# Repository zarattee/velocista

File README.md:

# velocista
 robot seguidor de linea

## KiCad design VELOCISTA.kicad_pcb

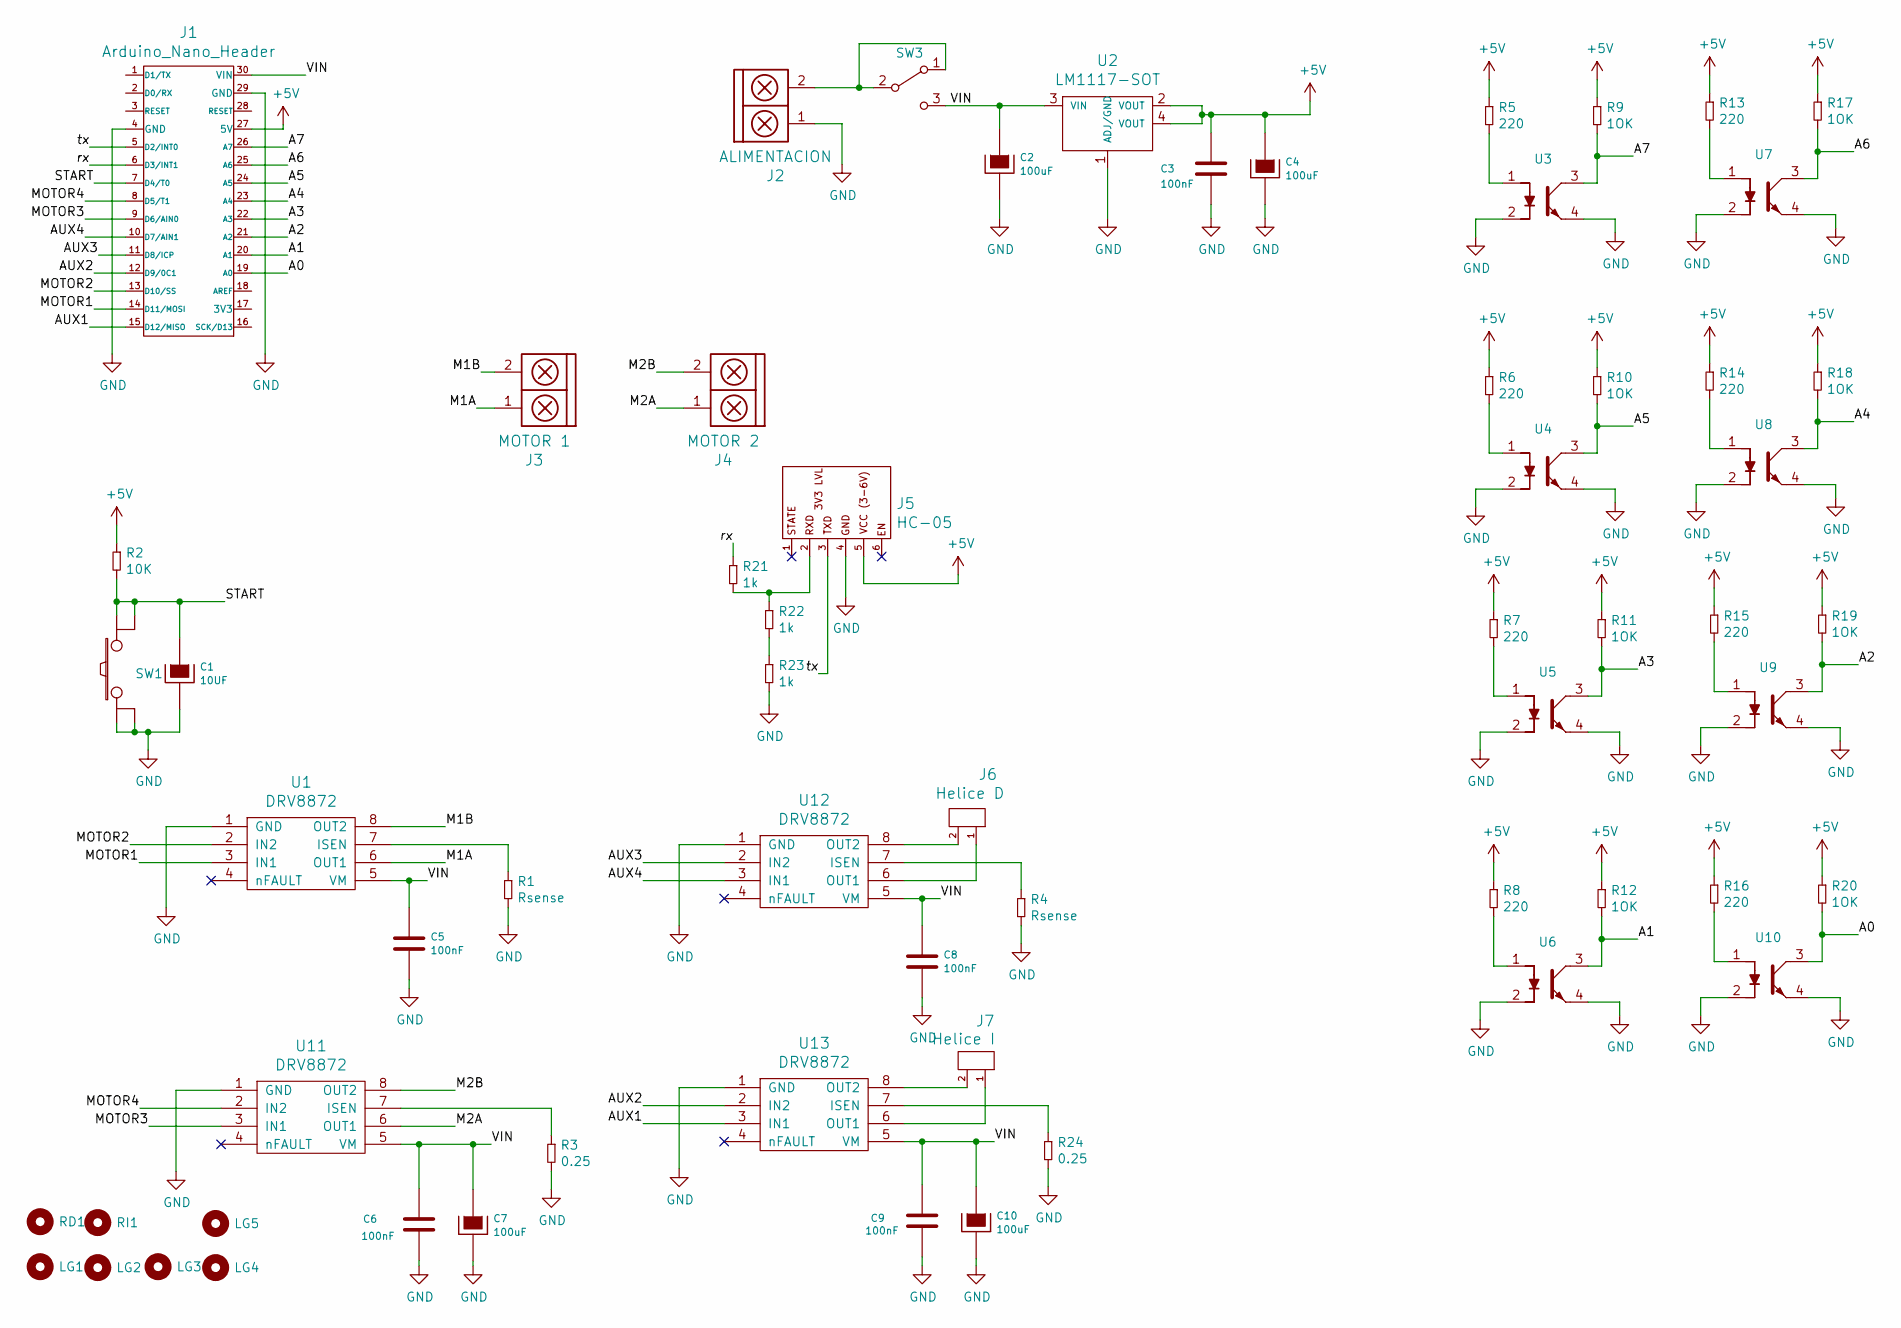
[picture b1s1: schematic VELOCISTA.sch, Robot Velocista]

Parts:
C1: 10UF; CAP_TAN_A
C2: 100uF; CAP_TAN_A
C3: 100nF; C_1206
C4: 100uF; CAP_ELEC_5x11mm
C5, C6, C8, C9: 100nF; CAP_0.1
C7, C10: 100uF; CAP_ELEC_8x11.5mm
J1: Arduino_Nano_Header; arduino_nano_header
J2: ALIMENTACION; BORNERA2_DUO
J3: MOTOR 1; BORNERA2_AZUL
J4: MOTOR 2; BORNERA2_AZUL
J5: HC-05
J6: Helice D; BORNERA2_DUO
J7: Helice I; BORNERA2_DUO
LG1: Mounting_Hole; LOGO_EESTN5
LG2: Mounting_Hole; Logo_Zarate
LG3: Mounting_Hole; Logo_Zarate_Nombre
LG4, LG5: Mounting_Hole; Logo_Rayo
R1, R4: Rsense; R_1206
R2: 10K; R_1206
R3, R24: 0.25; R_1206
R5, R6, R7, R8, R13, R14, R15, R16: 220; R_1206
R9, R10, R11, R12, R17, R18, R19, R20: 1OK; R_1206
R21, R22, R23: 1k; R_1206
RD1: Mounting_Hole; Pololu_Micro_Con_Soporte_Simple
RI1: Mounting_Hole; Pololu_Micro_Con_Soporte_Simple
SW1: SW_PUSH; Pulsador_4_SMD
SW3: SW_SPDT; SW_SPDT_TH_Vertical
U1, U11, U12, U13: DRV8872; SSOP-8
U2: LM1117-SOT; SOT223
U3, U4, U5, U6, U7, U8, U9, U10: QRE1113; QRE1113GR

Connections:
+5V: C3.1, C4.1, J1.27 (5V), J5.5, R2.1, R5.1, R6.1, R7.1, R8.1, R9.1, R10.1, R11.1, R12.1, R13.1, R14.1, R15.1, R16.1, R17.1, R18.1, R19.1, R20.1, U2.2 (VOUT), U2.4 (VOUT)
/A0: J1.19 (A0), R20.2, U10.3
/A1: J1.20 (A1), R12.2, U6.3
/A2: J1.21 (A2), R19.2, U9.3
/A3: J1.22 (A3), R11.2, U5.3
/A4: J1.23 (A4), R18.2, U8.3
/A5: J1.24 (A5), R10.2, U4.3
/A6: J1.25 (A6), R17.2, U7.3
/A7: J1.26 (A7), R9.2, U3.3
/AUX1: J1.15 (D12/MISO), U13.3 (IN1)
/AUX2: J1.12 (D9/0C1), U13.2 (IN2)
/AUX3: J1.11 (D8/ICP), U12.2 (IN2)
/AUX4: J1.10 (D7/AIN1), U12.3 (IN1)
/M1A: J3.1, U1.6 (OUT1)
/M1B: J3.2, U1.8 (OUT2)
/M2A: J4.1, U11.6 (OUT1)
/M2B: J4.2, U11.8 (OUT2)
/MOTOR1: J1.14 (D11/MOSI), U1.3 (IN1)
/MOTOR2: J1.13 (D10/SS), U1.2 (IN2)
/MOTOR3: J1.9 (D6/AIN0), U11.3 (IN1)
/MOTOR4: J1.8 (D5/T1), U11.2 (IN2)
/START: C1.1, J1.7 (D4/T0), R2.2, SW1.3, SW1.4
/VIN: C2.1, C5.1, C6.1, C7.1, C8.1, C9.1, C10.1, J1.30 (VIN), SW3.3 (C), U1.5 (VM), U2.3 (VIN), U11.5 (VM), U12.5 (VM), U13.5 (VM)
/rx: J1.6 (D3/INT1), R21.1
/tx: J1.5 (D2/INT0), J5.3
GND: C1.2, C2.2, C3.2, C4.2, C5.2, C6.2, C7.2, C8.2, C9.2, C10.2, J1.4 (GND), J1.29 (GND), J2.1, J5.4, R1.2, R3.2, R4.2, R23.2, R24.2, SW1.1, SW1.2, U1.1 (GND), U2.1 (ADJ/GND), U3.2, U3.4, U4.2, U4.4, U5.2, U5.4, U6.2, U6.4, U7.2, U7.4, U8.2, U8.4, U9.2, U9.4, U10.2, U10.4, U11.1 (GND), U12.1 (GND), U13.1 (GND)
unnamed: J2.2, SW3.1 (A), SW3.2 (B)
unnamed: J5.2, R21.2, R22.1
unnamed: J6.1, U12.6 (OUT1)
unnamed: J6.2, U12.8 (OUT2)
unnamed: J7.1, U13.6 (OUT1)
unnamed: J7.2, U13.8 (OUT2)
unnamed: R1.1, U1.7 (ISEN)
unnamed: R3.1, U11.7 (ISEN)
unnamed: R4.1, U12.7 (ISEN)
unnamed: R5.2, U3.1
unnamed: R6.2, U4.1
unnamed: R7.2, U5.1
unnamed: R8.2, U6.1
unnamed: R13.2, U7.1
unnamed: R14.2, U8.1
unnamed: R15.2, U9.1
unnamed: R16.2, U10.1
unnamed: R22.2, R23.1
unnamed: R24.1, U13.7 (ISEN)

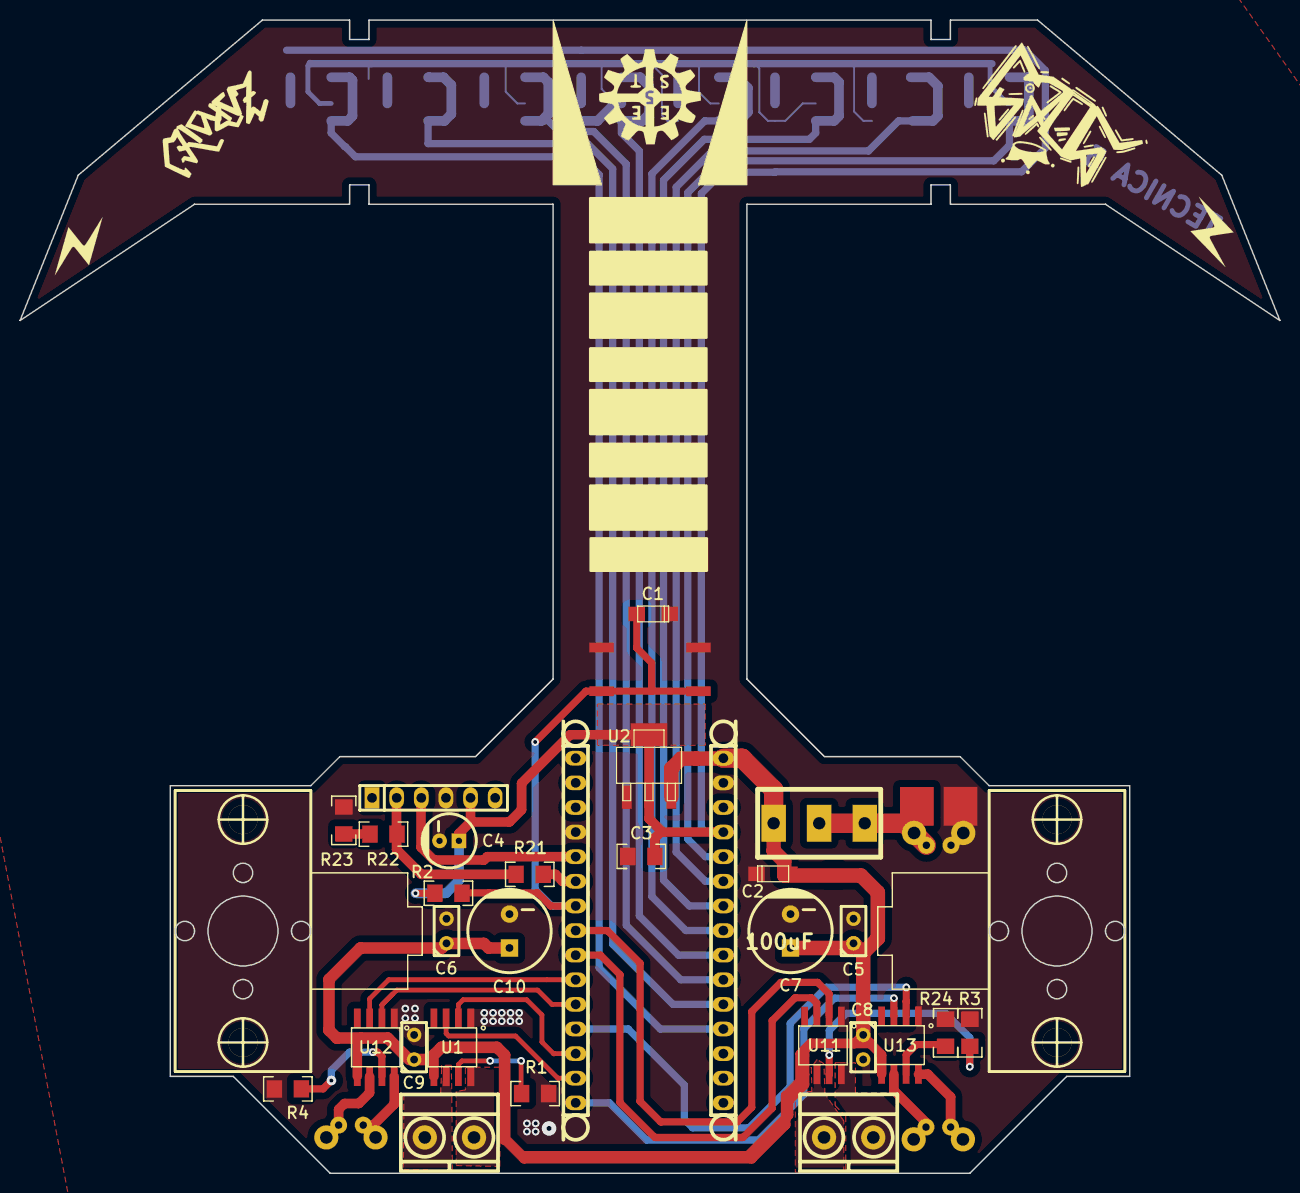
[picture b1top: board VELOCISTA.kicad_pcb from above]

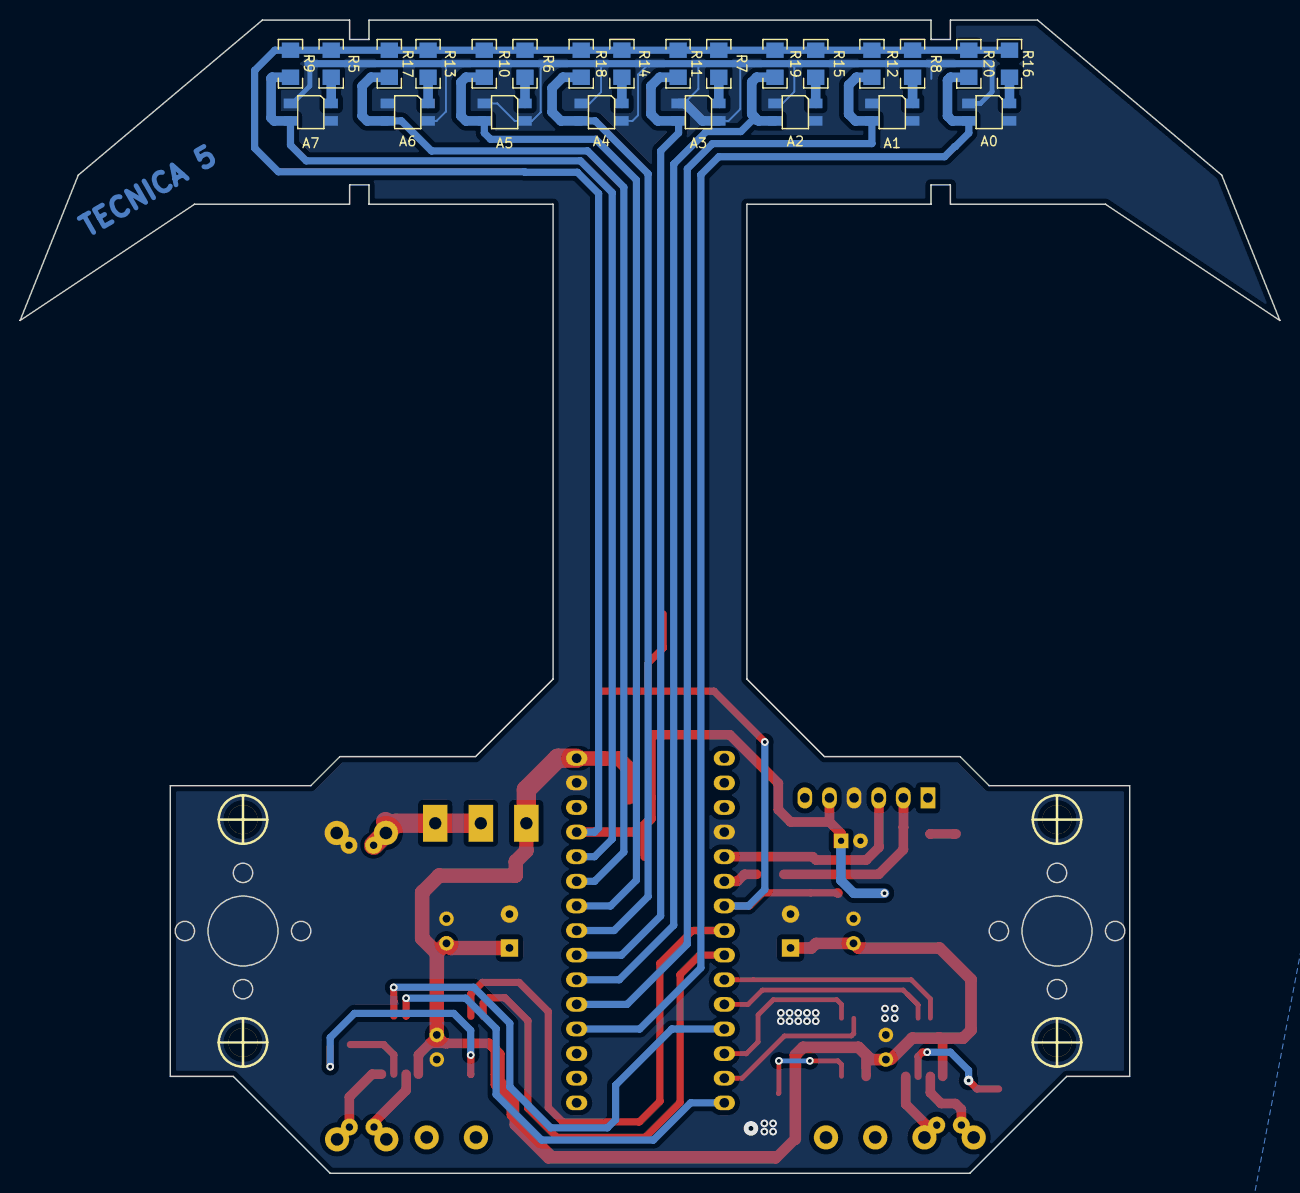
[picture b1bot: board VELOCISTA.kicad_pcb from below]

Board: 2 copper layers, 130.0 x 119.0 mm, 63 parts (24 on the bottom side), 45 nets.

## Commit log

2020-10-19 actualizacion inicial
2020-10-19 Pinout Atmega328p
    Grafica con descripcion de los pines del uC utilizado
2020-10-19 How to gerbers
    Guía para la generación de archivos de fabricación
2020-10-19 Ejemplo de modificación cruzada
    Recomendación para Elias
2020-10-20 se ignora variable de entorno
    se agrego un archivo no aceptable
2020-10-20 Render & BOM
    Generación de las imagenes del modelo 3D del proyecto desde diferentes vistas/configuraciones.
    Incorporación de la lista de materiales interactiva.
2020-10-20 eliminacion de archivos innecesarios
    eleminacion de archivos en conflicot con los archivo originales
2020-10-30 Actualizacion del archivo de taladros
    Se actualizo el archivo de taladros verificando el formato requerido por el fabricante.
    Se agrego la captura de pantalla de la configuracion utilizada para futura referencia.
    Se agrego el archivo comprimido con los gerbers enviados al fabricante.
2020-11-06 lista de componentes
    se agrego lista de componentees de la placa
2020-11-27 se agrega lista de componentes
    se agrega lista de componentes y
    como proveedor https://www.digikey.com
2021-01-08 Actualización BOM
    Se cambió el formato de la lista de materiales y se completaron los datos para un costeo inicial del equipo
2021-01-08 Actualizacion BOM II
    Cambios de formato y generación de la BOM inicial en pdf
2021-01-13 BOM PCBA
    Generé el archivo individual para enviar a presupuestar la adquisición de materiales
